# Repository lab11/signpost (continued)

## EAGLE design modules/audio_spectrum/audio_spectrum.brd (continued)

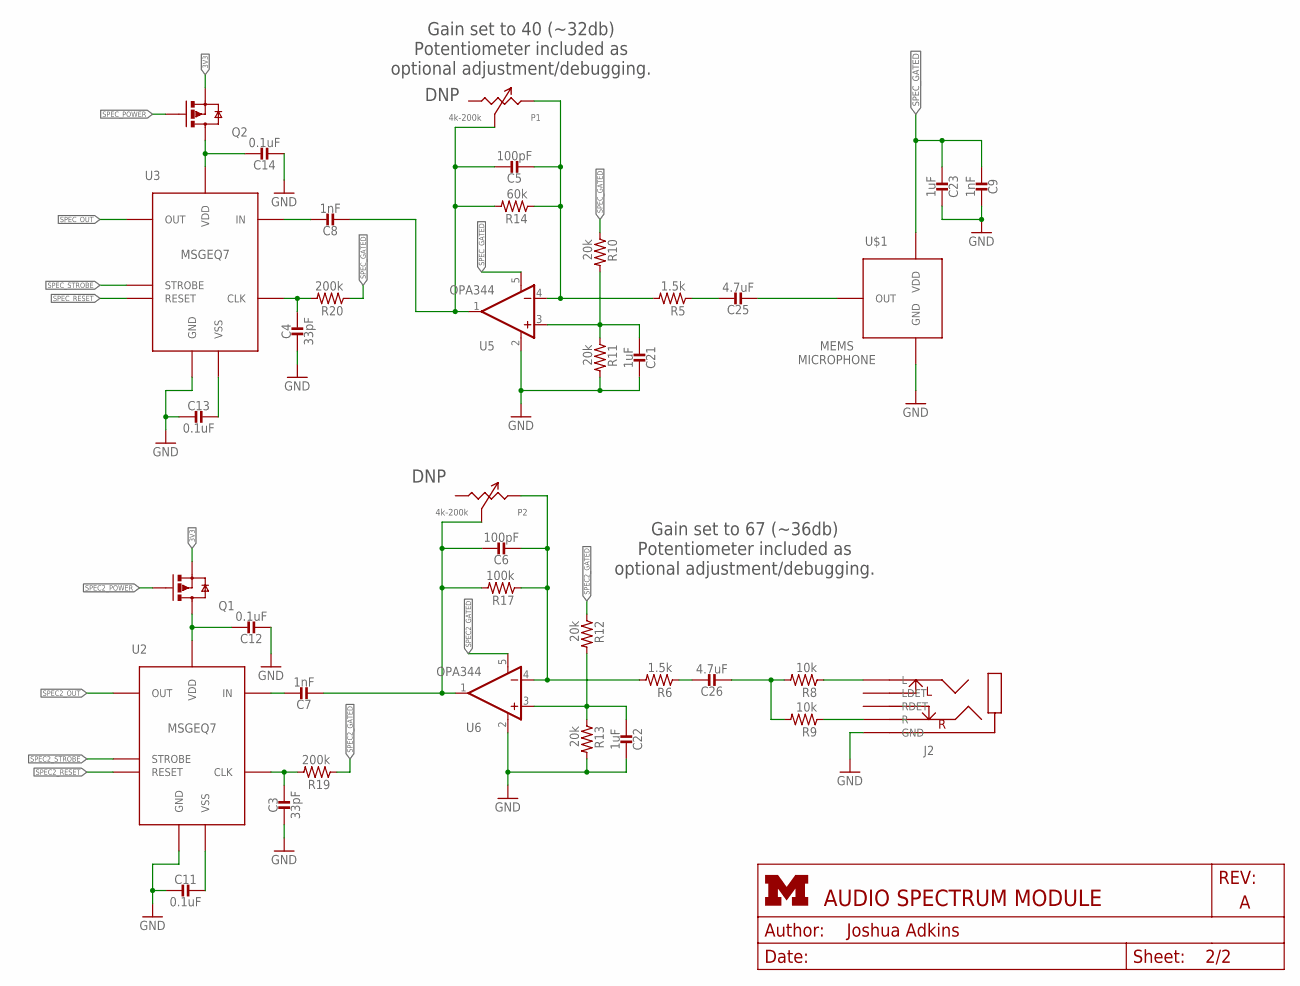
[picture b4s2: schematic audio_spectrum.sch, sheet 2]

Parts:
C3, C4: 33pF; 0603_CAP
C5, C6: 100pF; 0603_CAP
C7, C8, C9: 1nF; 0603_CAP
C11, C12, C13, C14: 0.1uF; 0603_CAP
C21, C22, C23: 1uF; 0603_CAP
C25, C26: 4.7uF; 0603_CAP
J2: AUDIO-JACK-VERTICAL
P1, P2: 4k-200k; TC33X-2
Q1, Q2: NX3008PBK; SOT23-3
R5, R6: 1.5k; 0603-RES
R8, R9: 10k; 0603-RES
R10, R11, R12, R13: 20k; 0603-RES
R14: 60k; 0603-RES
R17: 100k; 0603-RES
R19, R20: 200k; 0603-RES
U2, U3: MSGEQ7; DIP-8
U5, U6: OPA344; SOT23-5
U$1: MP23AB02B

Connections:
3V3: Q1.2 (S), Q2.2 (S); also elsewhere on the board
GND: C3.2, C4.2, C9.1, C11.2, C12.2, C13.2, C14.2, C21.1, C22.1, C23.1, J2.5 (GND), R11.2, R13.2, U2.6 (GND), U3.6 (GND), U5.2 (V-), U6.2 (V-), U$1.3 (GND); also elsewhere on the board
unnamed: C11.1, U2.2 (VSS)
unnamed: C3.1, R19.2, U2.8 (CLK)
unnamed: C7.1, U2.5 (IN)
unnamed: C6.1, C7.2, P2.3 (W), R17.2, U6.1 (OUT)
unnamed: C13.1, U3.2 (VSS)
unnamed: C4.1, R20.2, U3.8 (CLK)
unnamed: C8.1, U3.5 (IN)
unnamed: C5.1, C8.2, P1.3 (W), R14.2, U5.1 (OUT)
unnamed: C21.2, R10.2, R11.1, U5.3 (+IN)
unnamed: C26.2, R8.2, R9.2
unnamed: C22.2, R12.2, R13.1, U6.3 (+IN)
unnamed: C5.2, P1.2 (CW), R5.2, R14.1, U5.4 (-IN)
unnamed: C25.1, R5.1
unnamed: C6.2, P2.2 (CW), R6.2, R17.1, U6.4 (-IN)
unnamed: C26.1, R6.1
unnamed: J2.1 (R), R9.1
unnamed: J2.4 (L), R8.1
unnamed: C25.2, U$1.1 (OUT)
SPEC2_GATED: C12.1, Q1.3 (D), R12.1, R19.1, U2.1 (VDD), U6.5 (V+)
SPEC2_OUT: U2.3 (OUT); also elsewhere on the board
SPEC2_POWER: Q1.1 (G); also elsewhere on the board
SPEC2_RESET: U2.7 (RESET); also elsewhere on the board
SPEC2_STROBE: U2.4 (STROBE); also elsewhere on the board
SPEC_GATED: C9.2, C14.1, C23.2, Q2.3 (D), R10.1, R20.1, U3.1 (VDD), U5.5 (V+), U$1.2 (VDD)
SPEC_OUT: U3.3 (OUT); also elsewhere on the board
SPEC_POWER: Q2.1 (G); also elsewhere on the board
SPEC_RESET: U3.7 (RESET); also elsewhere on the board
SPEC_STROBE: U3.4 (STROBE); also elsewhere on the board

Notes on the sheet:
DNP
Gain set to 40 (~32db) Potentiometer included as optional adjustment/debugging.
Gain set to 67 (~36db) Potentiometer included as optional adjustment/debugging.

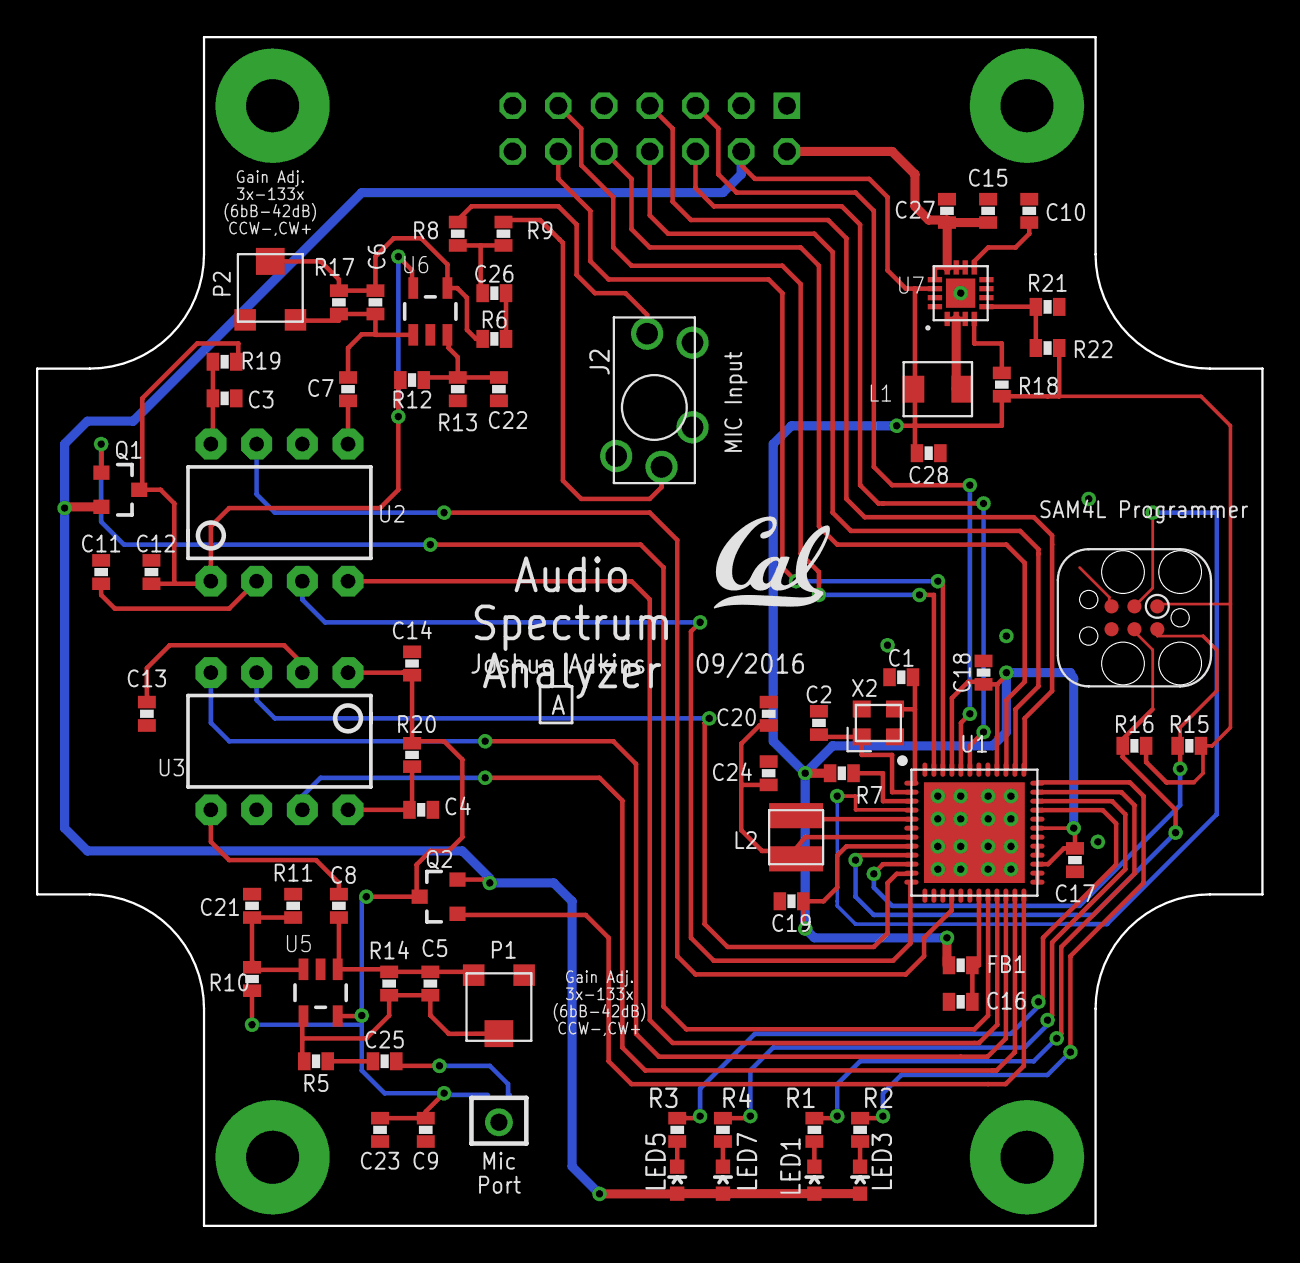
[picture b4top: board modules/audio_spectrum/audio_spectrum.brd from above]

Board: 2 copper layers, 68.1 x 66.0 mm, 73 parts (1 on the bottom side), 61 nets.

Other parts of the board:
U$2: UCB_CAL_200MIL

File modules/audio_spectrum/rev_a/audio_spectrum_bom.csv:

# Bill of Materials
# Converted from audio_spectrum_bom.xlsx
# Generated by bom_to_text.py

Part,Value,Device,Package,Description,DIGIKEY,MOUSER
C1,8pF,CAPACITOR0603_CAP,0603_CAP,0402 Capacitor,490-9670-1-ND,
C2,8pF,CAPACITOR0603_CAP,0603_CAP,0402 Capacitor,490-9670-1-ND,
C3,33pF,CAPACITOR0603_CAP,0603_CAP,0402 Capacitor,490-1415-1-ND,
C4,33pF,CAPACITOR0603_CAP,0603_CAP,0402 Capacitor,490-1415-1-ND,
C5,100pF,CAPACITOR0603_CAP,0603_CAP,0402 Capacitor,490-1427-1-ND,
C6,100pF,CAPACITOR0603_CAP,0603_CAP,0402 Capacitor,490-1427-1-ND,
C7,1nF,CAPACITOR0603_CAP,0603_CAP,0402 Capacitor,490-1494-1-ND,
C8,1nF,CAPACITOR0603_CAP,0603_CAP,0402 Capacitor,490-1494-1-ND,
C9,1nF,CAPACITOR0603_CAP,0603_CAP,0402 Capacitor,490-1494-1-ND,
C10,3.3nF,CAPACITOR0603_CAP,0603_CAP,0402 Capacitor,490-1503-1-ND,
C11,0.1uF,CAPACITOR0603_CAP,0603_CAP,0402 Capacitor,490-1532-1-ND,
C12,0.1uF,CAPACITOR0603_CAP,0603_CAP,0402 Capacitor,490-1532-1-ND,
C13,0.1uF,CAPACITOR0603_CAP,0603_CAP,0402 Capacitor,490-1532-1-ND,
C14,0.1uF,CAPACITOR0603_CAP,0603_CAP,0402 Capacitor,490-1532-1-ND,
C15,0.1uF,CAPACITOR0603_CAP,0603_CAP,0402 Capacitor,490-1532-1-ND,
C16,100nF,CAPACITOR0603_CAP,0603_CAP,0402 Capacitor,490-1532-1-ND,
C17,100nF,CAPACITOR0603_CAP,0603_CAP,0402 Capacitor,490-1532-1-ND,
C18,100nF,CAPACITOR0603_CAP,0603_CAP,0402 Capacitor,490-1532-1-ND,
C19,100nF,CAPACITOR0603_CAP,0603_CAP,0402 Capacitor,490-1532-1-ND,
C20,100nF,CAPACITOR0603_CAP,0603_CAP,0402 Capacitor,490-1532-1-ND,
C21,1uF,CAPACITOR0603_CAP,0603_CAP,0402 Capacitor,490-1536-1-ND,
C22,1uF,CAPACITOR0603_CAP,0603_CAP,0402 Capacitor,490-1536-1-ND,
C23,1uF,CAPACITOR0603_CAP,0603_CAP,0402 Capacitor,490-1536-1-ND,
C24,4.7uF,CAPACITOR0603_CAP,0603_CAP,0402 Capacitor,490-3297-1-ND,
C25,4.7uF,CAPACITOR0603_CAP,0603_CAP,0402 Capacitor,490-3297-1-ND,
C26,4.7uF,CAPACITOR0603_CAP,0603_CAP,0402 Capacitor,490-3297-1-ND,
C27,10uF,CAPACITOR0603_CAP,0603_CAP,0402 Capacitor,490-6405-1-ND,
C28,22uF,CAPACITOR0603_CAP,0603_CAP,0402 Capacitor,490-13241-1-ND,
FB1,1.5k,FERRITE_BEAD0603,0603_CAP,,490-5216-1-ND,
J1,MODULE_GENERIC,MODULE_GENERIC,MODULE_GENERIC,Module header and PCB  guildes for signposts,S9170-ND,
J2,AUDIO-JACK-VERTICAL,AUDIO-JACK-VERTICAL,AUDIO-JACK-VERTICAL,A vertical audio jack,,806-STX-3790-5N
L1,2.2uH,INDUCTORIHL,IHL-1212BZ-11,A very specific inductor,541-1322-1-ND,
L2,22uH,LHQ3NP,1212,LHQ3NP Inductor,490-5350-1-ND,
LED1,LED0603,LED0603,LED-0603,LED,160-1446-1-ND,
LED2,LED0603,LED0603,LED-0603,LED,160-1447-1-ND,
LED3,LED0603,LED0603,LED-0603,LED,160-1446-1-ND,
LED4,LED0603,LED0603,LED-0603,LED,160-1447-1-ND,
P1,4k-200k,POTTC33X,TC33X-2,Potentiometer,TC33X-2-204ECT-ND,
P2,4k-200k,POTTC33X,TC33X-2,Potentiometer,TC33X-2-204ECT-ND,
Q1,NX3008PBK,NX3008PBK,SOT23-3,MOSFET - P Channel,568-10499-1-ND,"771-NX3008PBK,215"
Q2,NX3008PBK,NX3008PBK,SOT23-3,MOSFET - P Channel,568-10499-1-ND,"771-NX3008PBK,215"
R1,1k,RESISTOR0603_RES,0603-RES,Resistor,RHM1.0KCGCT-ND,
R2,1k,RESISTOR0603_RES,0603-RES,Resistor,RHM1.0KCGCT-ND,
R3,1k,RESISTOR0603_RES,0603-RES,Resistor,RHM1.0KCGCT-ND,
R4,1k,RESISTOR0603_RES,0603-RES,Resistor,RHM1.0KCGCT-ND,
R5,1.5k,RESISTOR0603_RES,0603-RES,Resistor,RHM1.5KCGCT-ND,
R6,1.5k,RESISTOR0603_RES,0603-RES,Resistor,RHM1.5KCGCT-ND,
R7,10k,RESISTOR0603_RES,0603-RES,Resistor,RHM10.0KHCT-ND,
R8,10k,RESISTOR0603_RES,0603-RES,Resistor,RHM10.0KHCT-ND,
R9,10k,RESISTOR0603_RES,0603-RES,Resistor,RHM10.0KHCT-ND,
R10,20k,RESISTOR0603_RES,0603-RES,Resistor,RHM20KCGCT-ND,
R11,20k,RESISTOR0603_RES,0603-RES,Resistor,RHM20KCGCT-ND,
R12,20k,RESISTOR0603_RES,0603-RES,Resistor,RHM20KCGCT-ND,
R13,20k,RESISTOR0603_RES,0603-RES,Resistor,RHM20KCGCT-ND,
R14,60k,RESISTOR0603_RES,0603-RES,Resistor,RHM60.4KCLCT-ND,
R15,100k,RESISTOR0603_RES,0603-RES,Resistor,RHM100KCGCT-ND,
R16,100k,RESISTOR0603_RES,0603-RES,Resistor,RHM100KCGCT-ND,
R17,100k,RESISTOR0603_RES,0603-RES,Resistor,RHM100KCGCT-ND,
R18,100k,RESISTOR0603_RES,0603-RES,Resistor,RHM100KCGCT-ND,
R19,200k,RESISTOR0603_RES,0603-RES,Resistor,RHM200KCFCT-ND,
R20,200k,RESISTOR0603_RES,0603-RES,Resistor,RHM200KCFCT-ND,
R21,240k,RESISTOR0603_RES,0603-RES,Resistor,RHM240KCFCT-ND,
R22,750k,RESISTOR0603_RES,0603-RES,Resistor,RHM750KCFCT-ND,
U1,SAM4LC8AA,SAM4LC8AA,QFN-48-7MM,Atmel SAM4L microcontroller. ARM Cortex M4 with 512 KB Flash and 64 KB RAM,ATSAM4LC8AA-MU-ND,
U2,MSGEQ7,MSGEQ7,DIP-8,A CMOS spectrum analyzer,1568-1335-ND,
U3,MSGEQ7,MSGEQ7,DIP-8,A CMOS spectrum analyzer,1568-1335-ND,
U5,OPA344,OPA344,SOT23-5,Single gate rail-to-rail output op-amp. Inputs extend 300mV past rails.,OPA344NACT-ND,
U6,OPA344,OPA344,SOT23-5,Single gate rail-to-rail output op-amp. Inputs extend 300mV past rails.,OPA344NACT-ND,
U7,TLV62130,TLV62130,TQFN-16/3MM,"High Efficient 3A switching step-down regulator. 1V-5V out, 4V-17V in.",296-35978-1-ND,
U8,MP23AB02B,MP23AB02B,MP23AB02B,A pretty normal mems microphone,497-14947-1-ND,
X2,16MHz,FH1600015,FHXXX,Pericom Type FH 16 MHz 2.5 x 2.0 mm,FH1600015CT-ND,

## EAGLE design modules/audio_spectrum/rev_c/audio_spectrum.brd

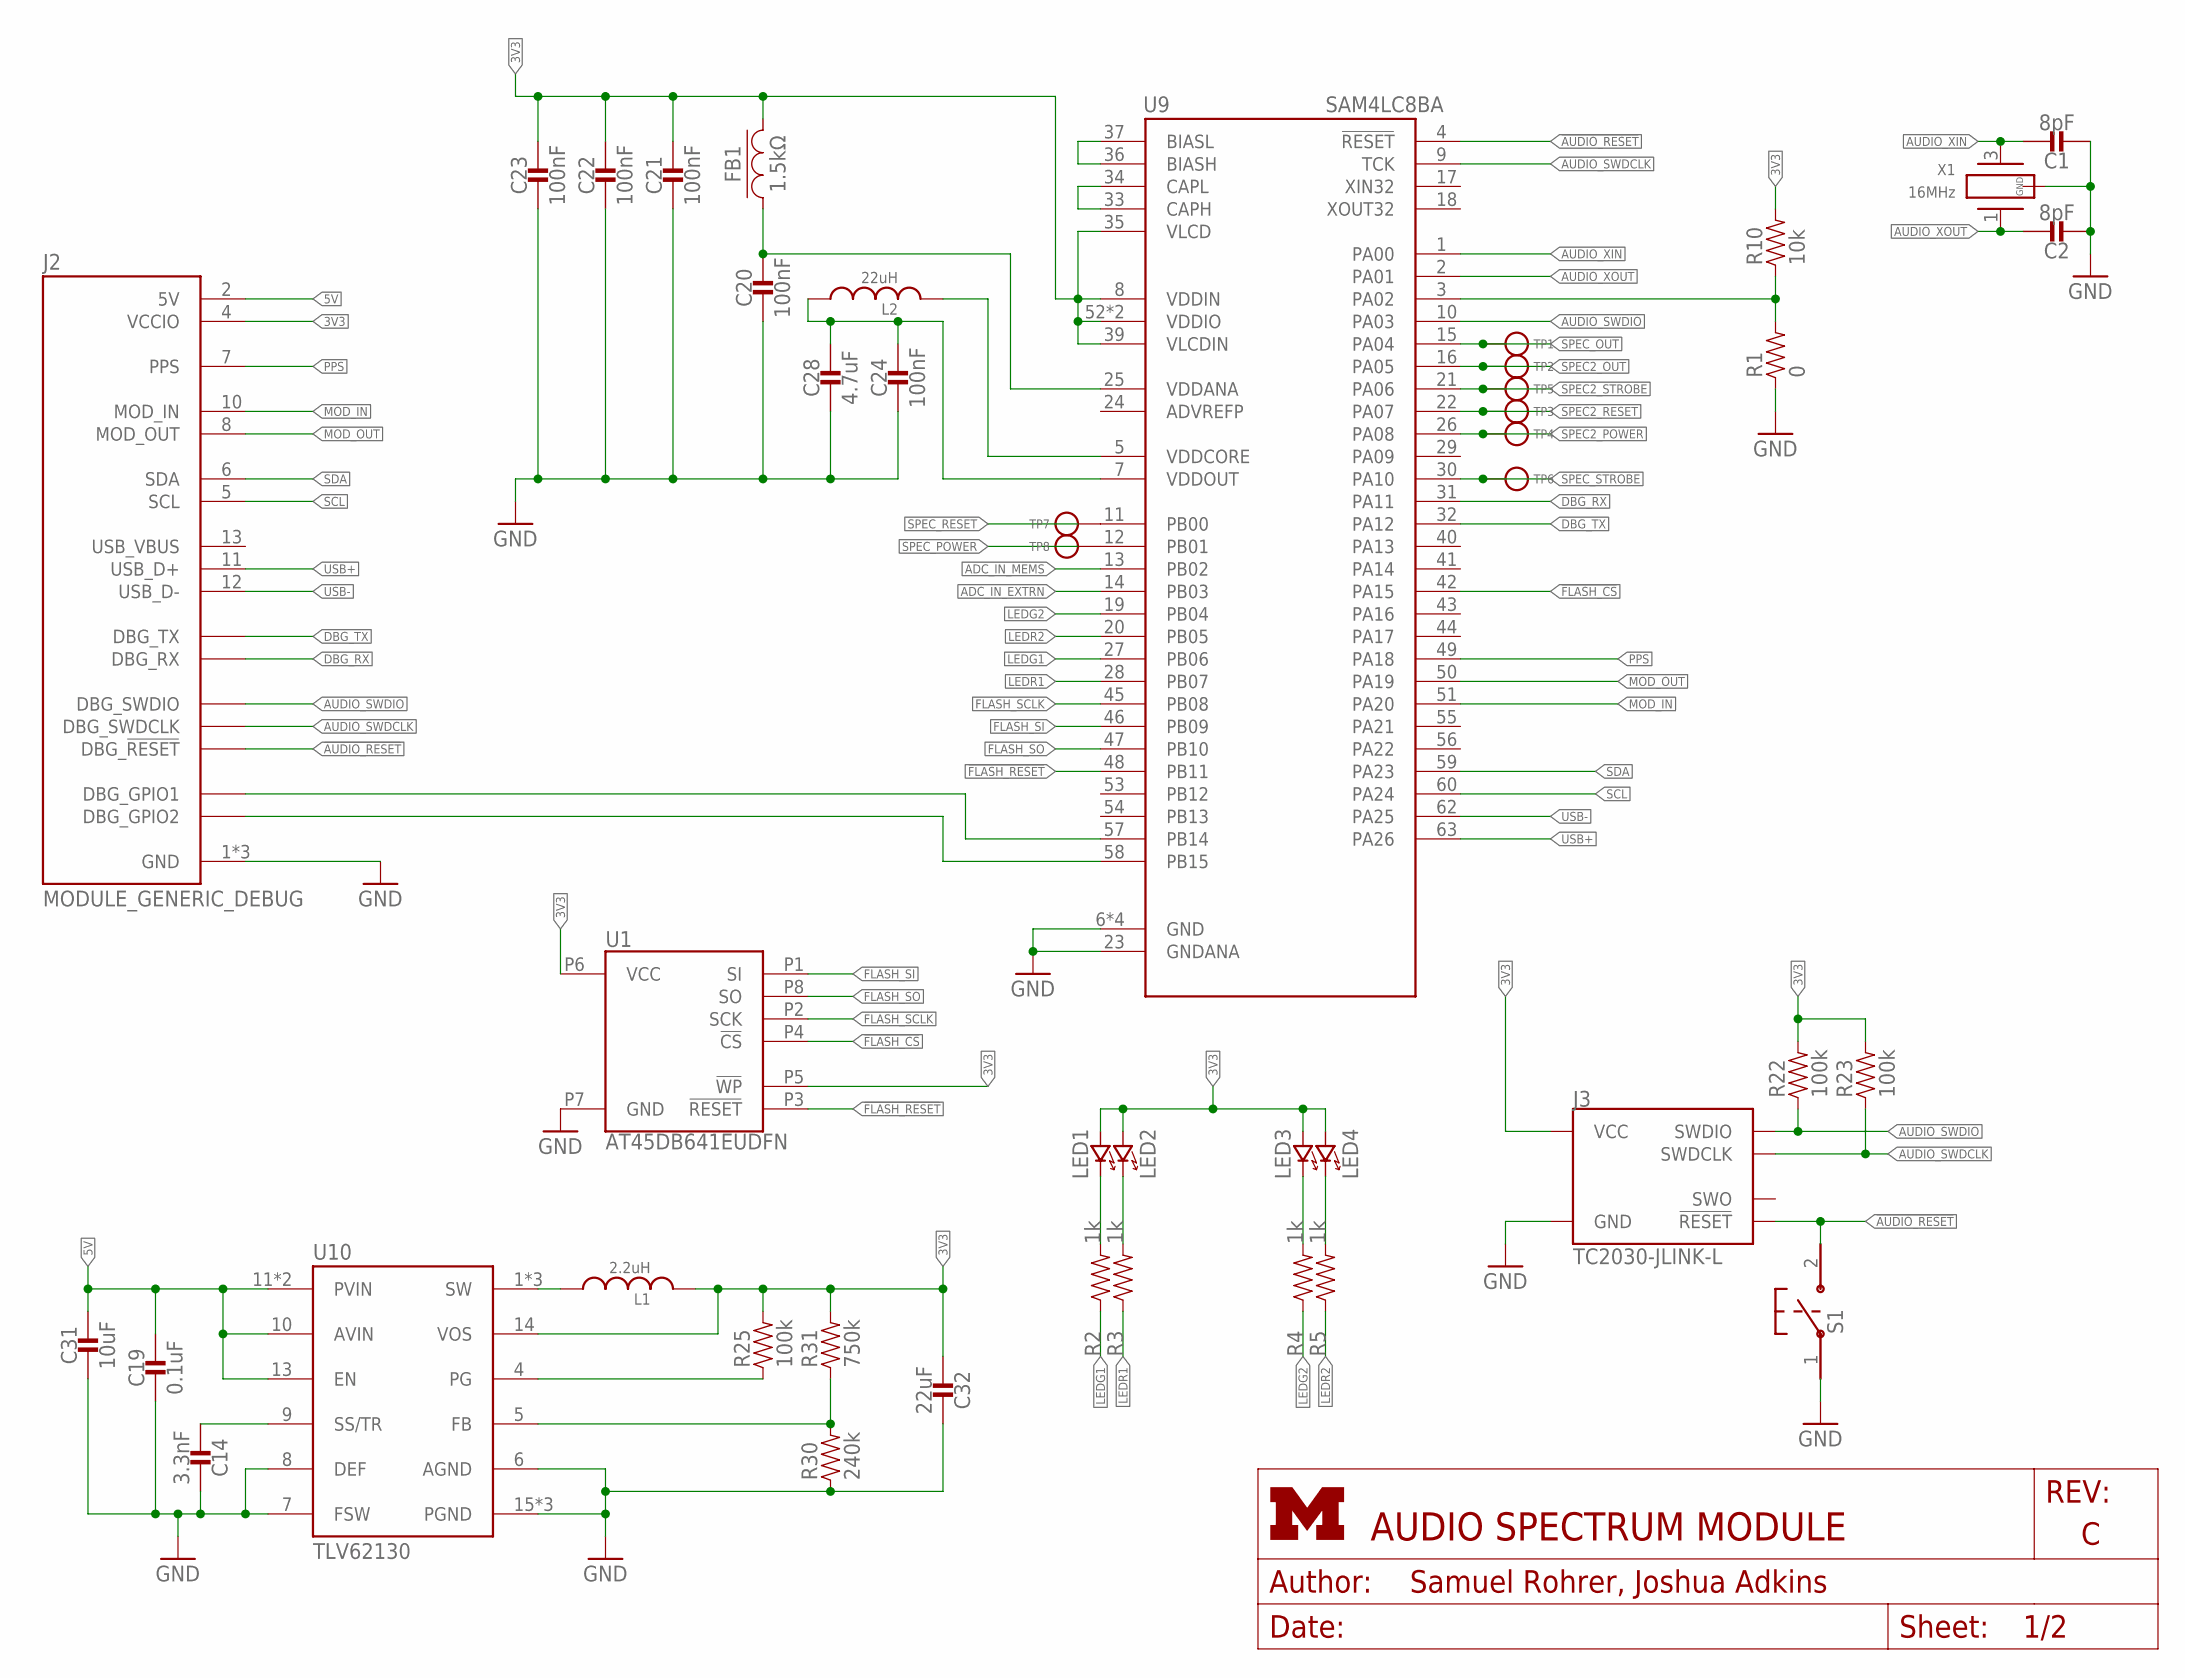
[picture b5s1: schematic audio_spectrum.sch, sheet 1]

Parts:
C1, C2: 8pF; 0603_CAP; DIGIKEY 478-1215-1-ND
C14: 3.3nF; 0603_CAP; DIGIKEY 490-1503-1-ND
C19: 0.1uF; 0603_CAP; DIGIKEY 490-1532-1-ND
C20, C21, C22, C23: 100nF; 0603_CAP; DIGIKEY 490-1532-1-ND
C24: 100nF; 0402_CAP; DIGIKEY 490-10777-1-ND
C28: 4.7uF; 0402_CAP; DIGIKEY 490-13252-1-ND
C31: 10uF; 0603_CAP; DIGIKEY 490-6405-1-ND
C32: 22uF; 0603_CAP; DIGIKEY 490-13241-1-ND
FB1: 1.5kΩ; 0603_CAP; DIGIKEY 490-5216-1-ND
J2: MODULE_GENERIC_DEBUG
J3: TC2030-JLINK-L; TC2030-IDC
L1: 2.2uH; IHL-1212BZ-11
L2: 22uH; 1212
LED1, LED3: LED0603; LED-0603; DIGIKEY 160-1446-1-ND
LED2, LED4: LED0603; LED-0603; DIGIKEY 160-1447-1-ND
R1: 0; 0603-RES; DIGIKEY 1276-3431-1-ND
R2: 1k; 0603-RES; DIGIKEY RHM1.0KDCT-N
R3, R4, R5: 1k; 0603-RES; DIGIKEY RHM1.0KDCT-ND
R10: 10k; 0603-RES; DIGIKEY RHM10.0KHCT-ND
R22, R23, R25: 100k; 0603-RES; DIGIKEY RHM100KCGCT-ND
R30: 240k; 0603-RES; DIGIKEY RHM240KCFCT-ND
R31: 750k; 0603-RES; DIGIKEY RHM750KCFCT-ND
S1: B3U-1000P
TP1, TP2, TP3, TP4, TP5, TP6, TP7, TP8: TEST_POINT_0.040IN; TESTPOINT_0.040IN
U1: AT45DB641EUDFN; UDFN-8-5MMX6MM
U9: SAM4LC8BA; QFN-64-9MM
U10: TLV62130; TQFN-16/3MM
X1: 16MHz; FHXXX

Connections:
3V3: C21.1, C22.1, C23.1, C32.2, FB1.2, J2.4 (VCCIO), J3.1 (VCC), L1.P$2 (2), LED1.A (ANODE), LED2.A (ANODE), LED3.A (ANODE), LED4.A (ANODE), R10.2, R22.2, R23.2, R25.2, R31.2, U1.P5 (!WP), U1.P6 (VCC), U9.8 (VDDIN), U9.35 (VLCD), U9.39 (VLCDIN), U9.52 (VDDIO), U9.61 (VDDIO), U10.14 (VOS); also elsewhere on the board
3VSWOUT: L1.P$1 (1), U10.1 (SW), U10.2 (SW), U10.3 (SW)
5V: C19.1, C31.1, J2.2 (5V), U10.10 (AVIN), U10.11 (PVIN), U10.12 (PVIN), U10.13 (EN)
!AUDIO_RESET: J2.20 (DBG_!RESET), J3.3 (!RESET), S1.2, U9.4 (!RESET)
!FLASH_CS: U1.P4 (!CS), U9.42 (PA15)
!FLASH_RESET: U1.P3 (!RESET), U9.48 (PB11)
ADC_IN_EXTRN: U9.14 (PB03); also elsewhere on the board
ADC_IN_MEMS: U9.13 (PB02); also elsewhere on the board
AUDIO_SWDCLK: J2.21 (DBG_SWDCLK), J3.4 (SWDCLK), R23.1, U9.9 (TCK)
AUDIO_SWDIO: J2.22 (DBG_SWDIO), J3.2 (SWDIO), R22.1, U9.10 (PA03)
AUDIO_XIN: C1.1, U9.1 (PA00), X1.3 (2)
AUDIO_XOUT: C2.1, U9.2 (PA01), X1.1
CONTROLLER_BUCK/LDO_N: R1.2, R10.1, U9.3 (PA02)
DBG_GPIO1: J2.16 (DBG_GPIO1), U9.57 (PB14)
DBG_GPIO2: J2.19 (DBG_GPIO2), U9.58 (PB15)
DBG_RX: J2.18 (DBG_RX), U9.31 (PA11)
DBG_TX: J2.17 (DBG_TX), U9.32 (PA12)
FLASH_SCLK: U1.P2 (SCK), U9.45 (PB08)
FLASH_SI: U1.P1 (SI), U9.46 (PB09)
FLASH_SO: U1.P8 (SO), U9.47 (PB10)
GND: C1.2, C2.2, C14.1, C19.2, C20.2, C21.2, C22.2, C23.2, C24.2, C28.2, C31.2, C32.1, J2.1 (GND), J2.14 (GND), J2.15 (GND), J3.5 (GND), R1.1, R30.1, S1.1, U1.P7 (GND), U9.6 (GND), U9.23 (GNDANA), U9.38 (GND), U9.64 (GND), U9.GND, U10.6 (AGND), U10.7 (FSW), U10.8 (DEF), U10.15 (PGND), U10.16 (PGND), U10.GND, X1.2 (GND), X1.4 (GND); also elsewhere on the board
LEDG1: R2.1, U9.27 (PB06)
LEDG2: R4.1, U9.19 (PB04)
LEDR1: R3.1, U9.28 (PB07)
LEDR2: R5.1, U9.20 (PB05)
MOD_IN: J2.10 (MOD_IN), U9.51 (PA20)
MOD_OUT: J2.8 (MOD_OUT), U9.50 (PA19)
unnamed: L2.P$2 (2), U9.5 (VDDCORE)
unnamed: LED1.C (CATHODE), R2.2
unnamed: TP7.TESTPOINT, U9.11 (PB00)
unnamed: LED2.C (CATHODE), R3.2
unnamed: TP8.TESTPOINT, U9.12 (PB01)
unnamed: LED4.C (CATHODE), R5.2
unnamed: C20.1, FB1.1, U9.25 (VDDANA)
unnamed: LED3.C (CATHODE), R4.2
unnamed: C14.2, U10.9 (SS/TR)
unnamed: R25.1, U10.4 (PG)
unnamed: R30.2, R31.1, U10.5 (FB)
unnamed: C24.1, C28.1, L2.P$1 (1), U9.7 (VDDOUT)
unnamed: U9.36 (BIASH), U9.37 (BIASL)
unnamed: U9.33 (CAPH), U9.34 (CAPL)
PPS: J2.7 (PPS), U9.49 (PA18)
SCL: J2.5 (SCL), U9.60 (PA24)
SDA: J2.6 (SDA), U9.59 (PA23)
SPEC2_OUT: TP2.TESTPOINT, U9.16 (PA05); also elsewhere on the board
SPEC2_POWER: TP4.TESTPOINT, U9.26 (PA08); also elsewhere on the board
SPEC2_RESET: TP3.TESTPOINT, U9.22 (PA07); also elsewhere on the board
SPEC2_STROBE: TP5.TESTPOINT, U9.21 (PA06); also elsewhere on the board
SPEC_OUT: TP1.TESTPOINT, U9.15 (PA04); also elsewhere on the board
SPEC_STROBE: TP6.TESTPOINT, U9.30 (PA10); also elsewhere on the board
USB+: J2.11 (USB_D+), U9.63 (PA26)
USB-: J2.12 (USB_D-), U9.62 (PA25)

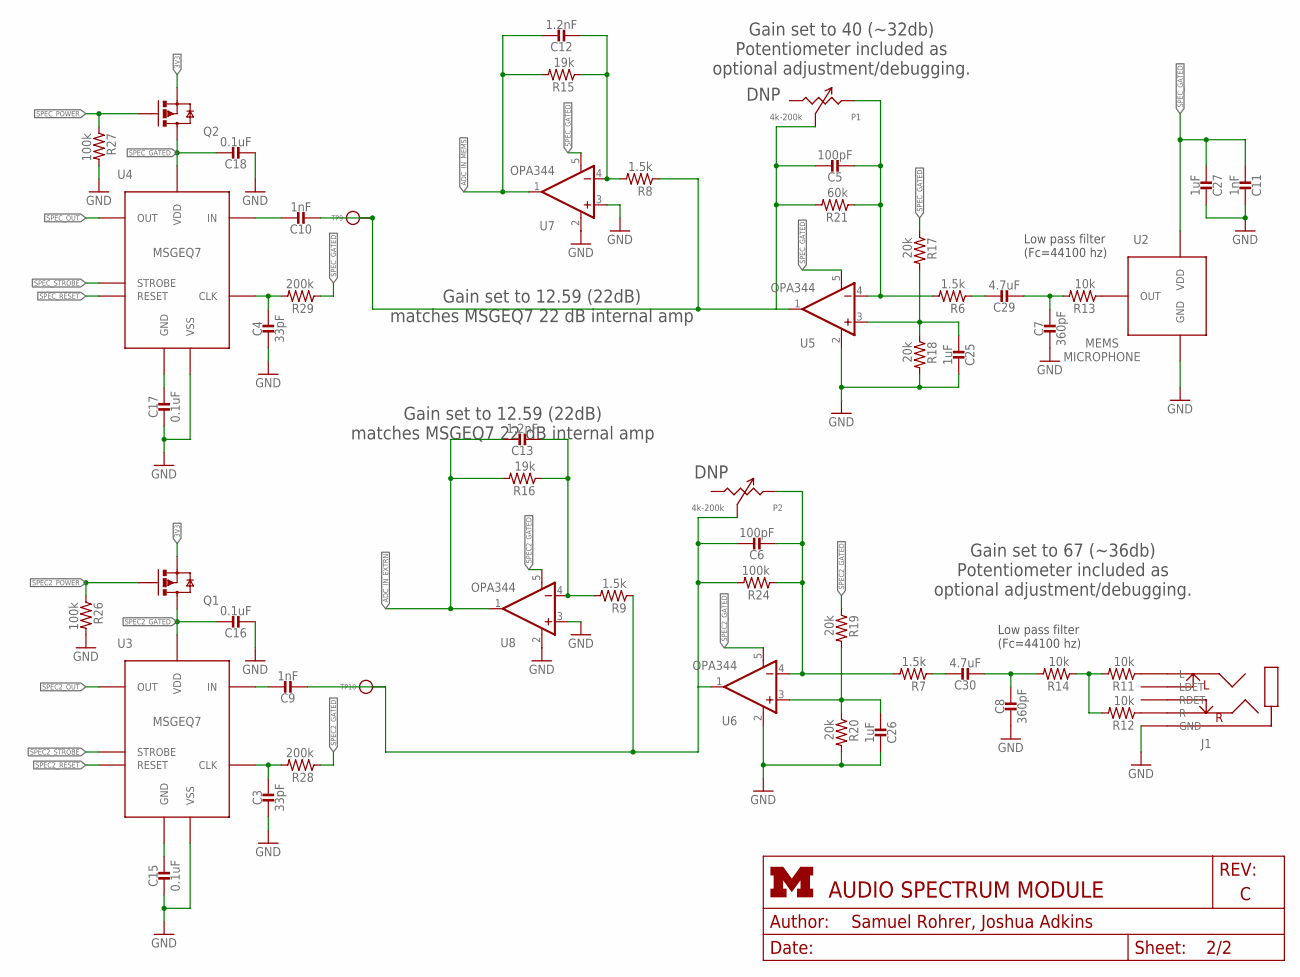
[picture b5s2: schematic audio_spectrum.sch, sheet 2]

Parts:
C3, C4: 33pF; 0603_CAP; DIGIKEY 490-1415-1-ND
C5, C6: 100pF; 0603_CAP; DIGIKEY 490-1427-1-ND
C7, C8: 360pF; 0603_CAP; DIGIKEY 490-1440-1-ND
C9, C10, C11: 1nF; 0603_CAP; DIGIKEY 490-1494-1-ND
C12, C13: 1.2nF; 0603_CAP; DIGIKEY 490-13298-1-ND
C15, C16, C17, C18: 0.1uF; 0603_CAP; DIGIKEY 490-1532-1-ND
C25, C26, C27: 1uF; 0603_CAP; DIGIKEY 490-1536-1-ND
C29, C30: 4.7uF; 0603_CAP; DIGIKEY 490-3297-1-ND
J1: AUDIO-JACK-VERTICAL
P1, P2: 4k-200k; TC33X-2
Q1, Q2: NX3008PBK; SOT23-3
R6, R7, R8, R9: 1.5k; 0603-RES; DIGIKEY RHM1.5KCGCT-ND
R11, R12, R13, R14: 10k; 0603-RES; DIGIKEY RHM10.0KHCT-ND
R15, R16: 19k; 0603-RES; DIGIKEY RHM19.1KCFCT-ND
R17, R18, R19, R20: 20k; 0603-RES; DIGIKEY RHM20KCGCT-ND
R21: 60k; 0603-RES; DIGIKEY RHM60.4KCLCT-ND
R24, R26, R27: 100k; 0603-RES; DIGIKEY RHM100KCGCT-ND
R28, R29: 200k; 0603-RES; DIGIKEY RHM200KCFCT-ND
TP9, TP10: TEST_POINT_0.040IN; TESTPOINT_0.040IN
U2: MP23AB02B
U3, U4: MSGEQ7; DIP-8
U5, U6, U7, U8: OPA344; SOT23-5; DIGIKEY OPA344NACT-ND

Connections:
3V3: Q1.2 (S), Q2.2 (S); also elsewhere on the board
ADC_IN_EXTRN: C13.1, R16.2, U8.1 (OUT); also elsewhere on the board
ADC_IN_MEMS: C12.1, R15.2, U7.1 (OUT); also elsewhere on the board
GND: C3.2, C4.2, C7.2, C8.2, C11.1, C15.2, C16.2, C17.2, C18.2, C25.1, C26.1, C27.1, J1.5 (GND), R18.2, R20.2, R26.2, R27.2, U2.3 (GND), U3.2 (VSS), U4.2 (VSS), U5.2 (V-), U6.2 (V-), U7.2 (V-), U7.3 (+IN), U8.2 (V-), U8.3 (+IN); also elsewhere on the board
N87: C6.1, C9.2, P2.3 (W), R9.1, R24.2, TP10.TESTPOINT, U6.1 (OUT)
N90: C5.1, C10.2, P1.3 (W), R8.1, R21.2, TP9.TESTPOINT, U5.1 (OUT)
unnamed: C15.1, U3.6 (GND)
unnamed: C3.1, R28.2, U3.8 (CLK)
unnamed: C9.1, U3.5 (IN)
unnamed: C7.1, C29.2, R13.2
unnamed: C4.1, R29.2, U4.8 (CLK)
unnamed: C10.1, U4.5 (IN)
unnamed: C13.2, R9.2, R16.1, U8.4 (-IN)
unnamed: C25.2, R17.2, R18.1, U5.3 (+IN)
unnamed: R11.2, R12.2, R14.1
unnamed: C26.2, R19.2, R20.1, U6.3 (+IN)
unnamed: C5.2, P1.2 (CW), R6.2, R21.1, U5.4 (-IN)
unnamed: C29.1, R6.1
unnamed: C6.2, P2.2 (CW), R7.2, R24.1, U6.4 (-IN)
unnamed: C30.1, R7.1
unnamed: J1.1 (R), R12.1
unnamed: J1.4 (L), R11.1
unnamed: R13.1, U2.1 (OUT)
unnamed: C17.1, U4.6 (GND)
unnamed: C8.1, C30.2, R14.2
unnamed: C12.2, R8.2, R15.1, U7.4 (-IN)
SPEC2_GATED: C16.1, Q1.3 (D), R19.1, R28.1, U3.1 (VDD), U6.5 (V+), U8.5 (V+)
SPEC2_OUT: U3.3 (OUT); also elsewhere on the board
SPEC2_POWER: Q1.1 (G), R26.1; also elsewhere on the board
SPEC2_RESET: U3.7 (RESET); also elsewhere on the board
SPEC2_STROBE: U3.4 (STROBE); also elsewhere on the board
SPEC_GATED: C11.2, C18.1, C27.2, Q2.3 (D), R17.1, R29.1, U2.2 (VDD), U4.1 (VDD), U5.5 (V+), U7.5 (V+)
SPEC_OUT: U4.3 (OUT); also elsewhere on the board
SPEC_POWER: Q2.1 (G), R27.1
SPEC_RESET: U4.7 (RESET)
SPEC_STROBE: U4.4 (STROBE); also elsewhere on the board

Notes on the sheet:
DNP
Gain set to 40 (~32db) Potentiometer included as optional adjustment/debugging.
Gain set to 67 (~36db) Potentiometer included as optional adjustment/debugging.
Low pass filter (Fc=44100 hz)
Gain set to 12.59 (22dB) matches MSGEQ7 22 dB internal amp

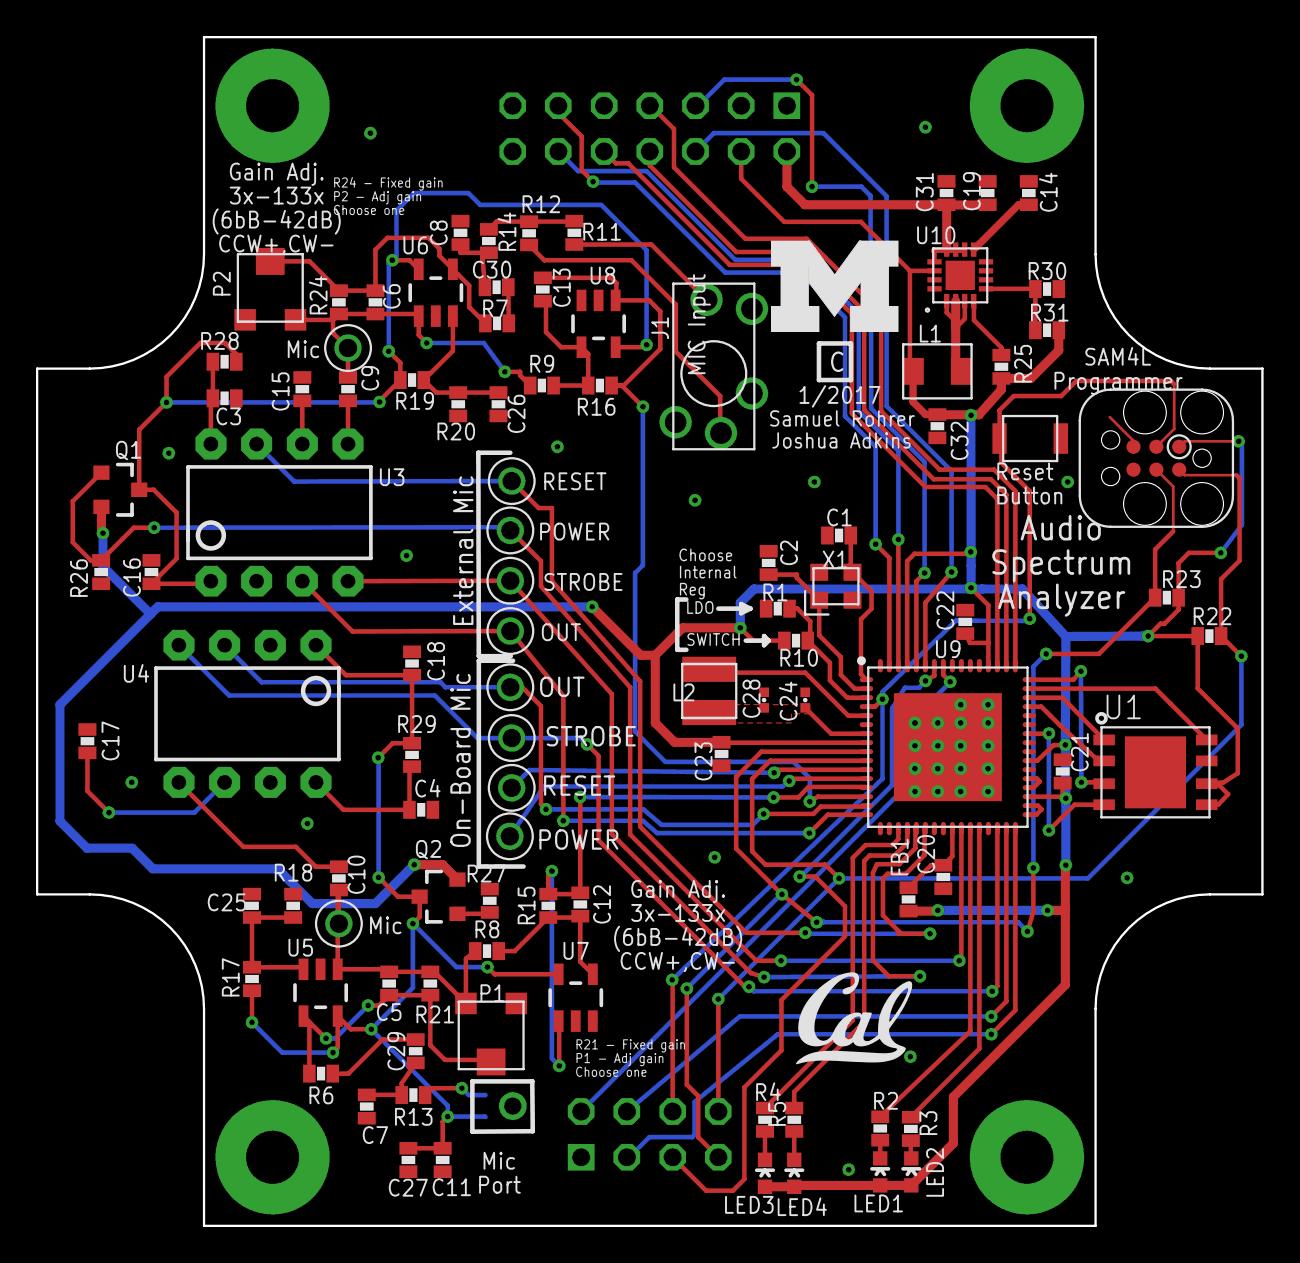
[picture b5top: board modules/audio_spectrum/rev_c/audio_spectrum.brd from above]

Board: 2 copper layers, 68.1 x 66.0 mm, 101 parts (1 on the bottom side), 77 nets.

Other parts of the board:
U$1: UMICH_SOLID_200MIL
U$2: UCB_CAL_200MIL

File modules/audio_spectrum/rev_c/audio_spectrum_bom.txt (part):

# Bill of Materials
# Converted from audio_spectrum_bom.xlsx
# Generated by bom_to_text.py
#
# Qty  Value                 Device                Package               Parts                                              Description                                                              DIGIKEY                MOUSER             NEWARK
1      8pF                   CAPACITOR0603_CAP     0603_CAP              C1, C2                                             0402 Capacitor                                                           478-1215-1-ND                             
5      1.2nF                 CAPACITOR0603_CAP     0603_CAP              C12, C13                                           0402 Capacitor                                                           490-13298-1-ND                            
2      3.3nF                 CAPACITOR0603_CAP     0603_CAP              C14                                                0402 Capacitor                                                           490-1503-1-ND                             
4      0.1uF                 CAPACITOR0603_CAP     0603_CAP              C15, C16, C17, C18, C19                            0402 Capacitor                                                           490-1532-1-ND                             
1      100nF                 CAPACITOR0603_CAP     0603_CAP              C20, C21, C22, C23                                 0402 Capacitor                                                           490-1532-1-ND                             
6      100nF                 CAPACITOR0402_CAP     0402_CAP              C24                                                0402 Capacitor                                                           490-10777-1-ND                            
1      1uF                   CAPACITOR0603_CAP     0603_CAP              C25, C26, C27                                      0402 Capacitor                                                           490-1536-1-ND                             
4      4.7uF                 CAPACITOR0402_CAP     0402_CAP              C28                                                0402 Capacitor                                                           490-13252-1-ND                            
2      4.7uF                 CAPACITOR0603_CAP     0603_CAP              C29, C30                                           0402 Capacitor                                                           490-3297-1-ND                             
1      33pF                  CAPACITOR0603_CAP     0603_CAP              C3, C4                                             0402 Capacitor                                                           490-1415-1-ND                             
4      10uF                  CAPACITOR0603_CAP     0603_CAP              C31                                                0402 Capacitor                                                           490-6405-1-ND                             
1      22uF                  CAPACITOR0603_CAP     0603_CAP              C32                                                0402 Capacitor                                                           490-13241-1-ND                            
1      100pF                 CAPACITOR0603_CAP     0603_CAP              C5, C6                                             0402 Capacitor                                                           490-1427-1-ND                             
2      360pF                 CAPACITOR0603_CAP     0603_CAP              C7, C8                                             0402 Capacitor                                                           490-1440-1-ND                             
1      1nF                   CAPACITOR0603_CAP     0603_CAP              C9, C10, C11                                       0402 Capacitor                                                           490-1494-1-ND                             
3      1.5k                  FERRITE_BEAD0603      0603_CAP              FB1                                                                                                                         490-5216-1-ND                             
3      AUDIO-JACK-VERTICAL   AUDIO-JACK-VERTICAL   AUDIO-JACK-VERTICAL   J1                                                 A vertical audio jack                                                                           806-STX-3790-5N    
3      MODULE_GENERIC_DEBUG  MODULE_GENERIC_DEBUG  MODULE_GENERIC_DEBUG  J2                                                 The debug version of the signpost module header                          S9170-ND                                  
1      TC2030-JLINK-L        TC2030-JLINK-L        TC2030-IDC            J3                                                                                                                                                                    
2      2.2uH                 INDUCTORIHL           IHL-1212BZ-11         L1                                                 A very specific inductor                                                 541-1322-1-ND                             
4      22uH                  LHQ3NP                1212                  L2                                                 LHQ3NP Inductor                                                          490-5350-1-ND                             
1      LED0603               LED0603               LED-0603              LED1, LED3                                         LED                                                                      160-1446-1-ND                             
1      LED0603               LED0603               LED-0603              LED2, LED4                                         LED                                                                      160-1447-1-ND                             
1      4k-200k               POTTC33X              TC33X-2               P1, P2                                             Potentiometer                                                            TC33X-2-204ECT-ND                         
1      NX3008PBK             NX3008PBK             SOT23-3               Q1, Q2                                             MOSFET - P Channel                                                       568-10499-1-ND         771-NX3008PBK,215  74T4665
2      0                     RESISTOR0603_RES      0603-RES              R1                                                 Resistor                                                                 1276-3431-1-ND                            
2      10k                   RESISTOR0603_RES      0603-RES              R10, R11, R13, R14                                 Resistor                                                                 RHM10.0KHCT-ND                            
1      10k                   RESISTOR0603_RES      0603-RES              R12                                                Resistor                                                                 RHM10.0KHCT-ND                            
2      19k                   RESISTOR0603_RES      0603-RES              R15, R16                                           Resistor                                                                 RHM19.1KCFCT-ND                           
2      20k                   RESISTOR0603_RES      0603-RES              R17, R18, R19, R20                                 Resistor                                                                 RHM20KCGCT-ND                             
1      1k                    RESISTOR0603_RES      0603-RES              R2                                                 Resistor                                                                 RHM1.0KDCT-N                              
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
